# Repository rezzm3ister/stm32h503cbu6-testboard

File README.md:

# stm32h503cbu6-testboard
h503cbu6 testboard based on the previous g4 testboard

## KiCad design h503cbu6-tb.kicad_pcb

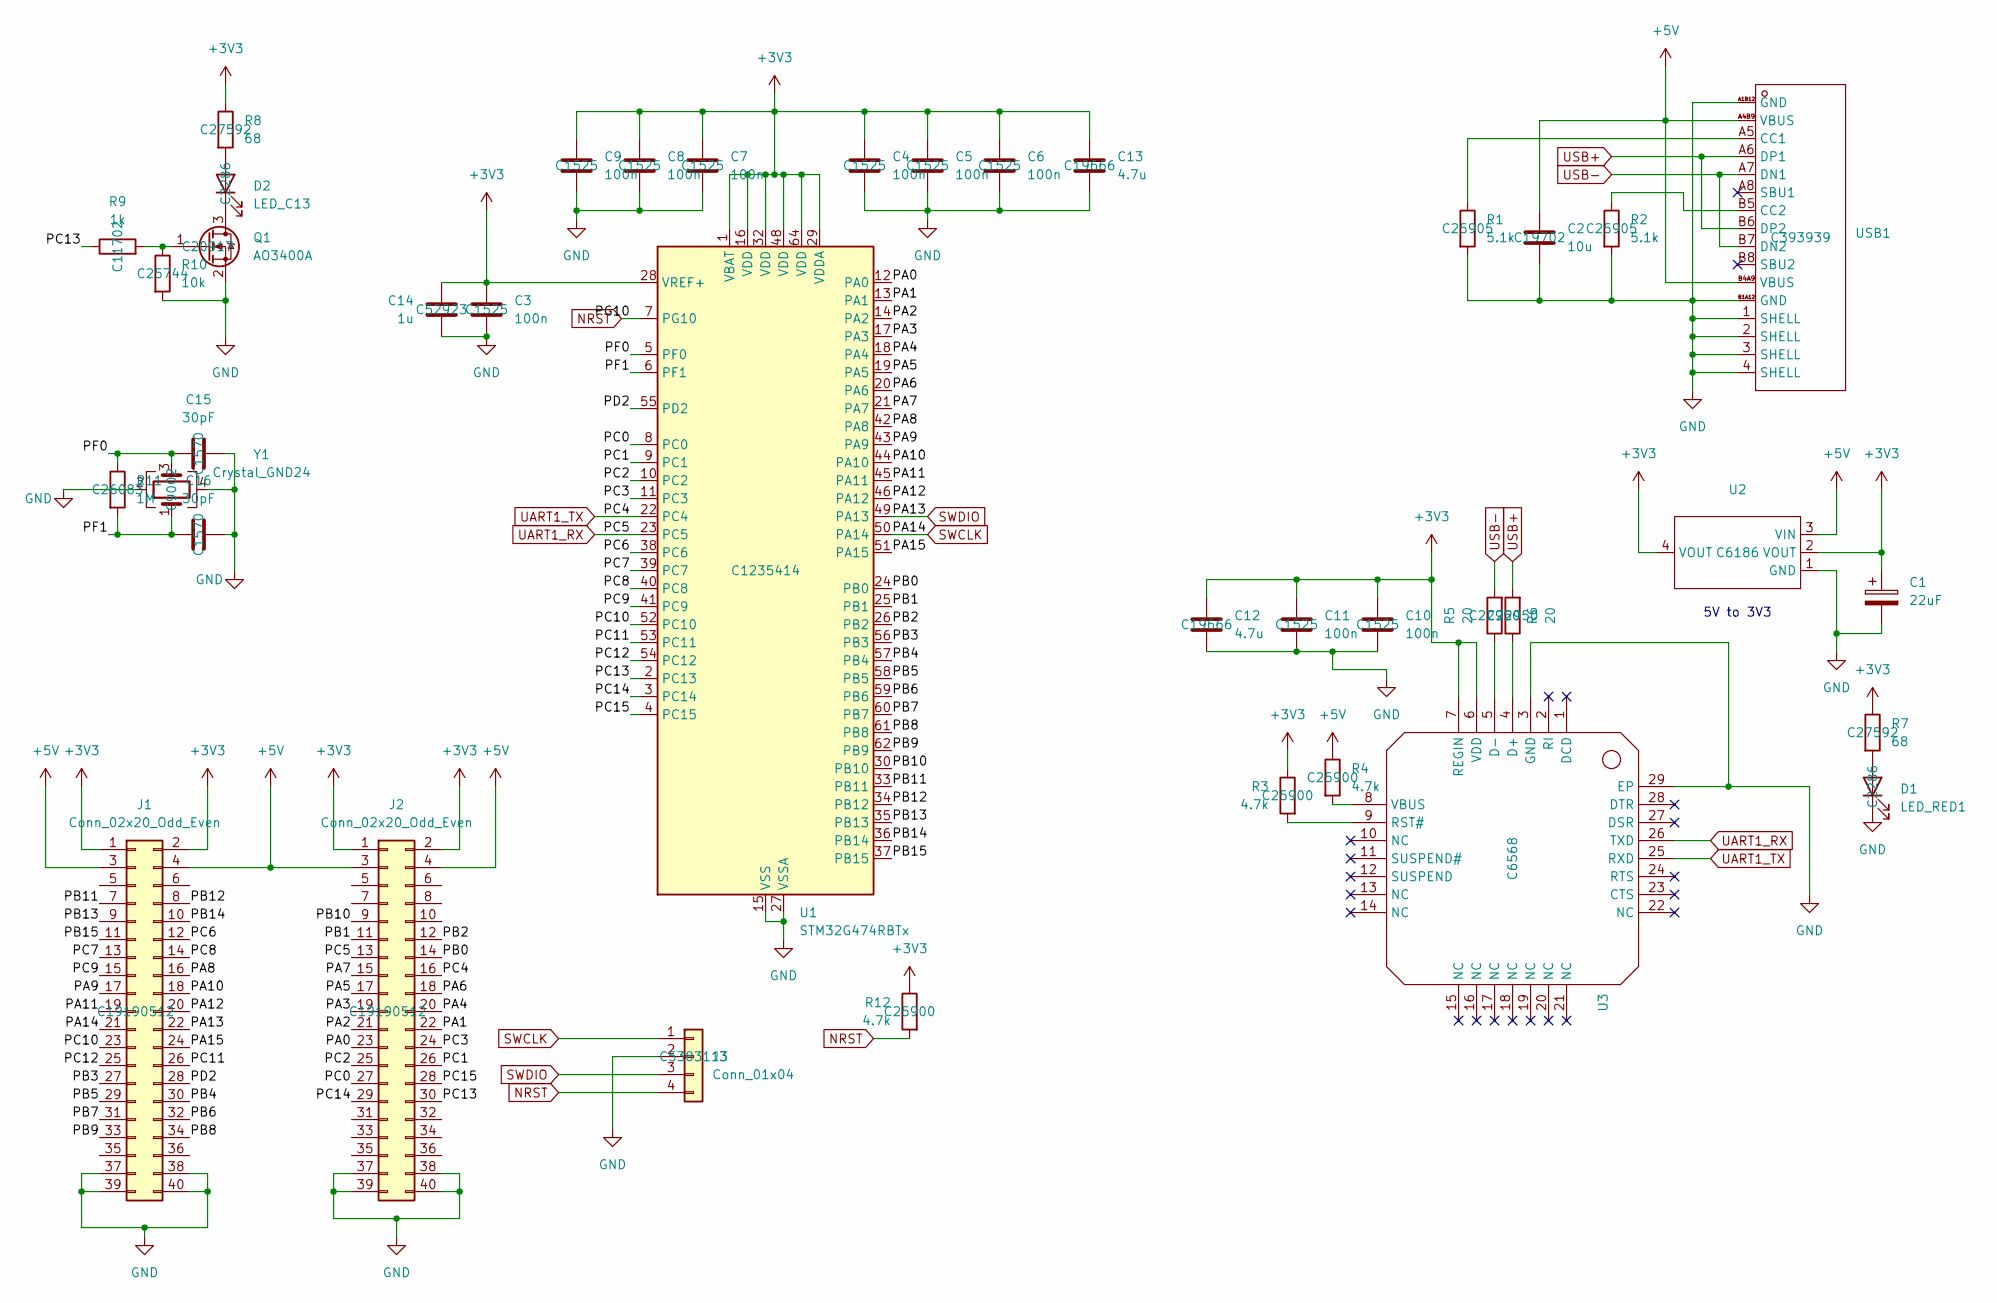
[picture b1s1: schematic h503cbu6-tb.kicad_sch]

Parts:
C1: 22uF; CP_EIA-3216-18_Kemet-A; LCSC C7182
C2: 10u; C_0603_1608Metric; LCSC C19702
C3, C4, C5, C6, C7, C8, C9, C10, C11: 100n; C_0402_1005Metric; LCSC C1525
C12, C13: 4.7u; C_0603_1608Metric; LCSC C19666
C14: 1u; C_0603_1608Metric; LCSC C52923
C15, C16: 30pF; C_0402_1005Metric; LCSC C1570
D1: LED_RED1; LED_0603_1608Metric; LCSC C2286
D2: LED_C13; LED_0603_1608Metric; LCSC C2286
J1, J2: Conn_02x20_Odd_Even; PinHeader_2x20_P2.54mm_Vertical; LCSC C19190512
J3: Conn_01x04; PinHeader_1x04_P2.54mm_Vertical; LCSC C5383113
Q1: AO3400A; SOT-23; LCSC C20917
R1, R2: 5.1k; R_0402_1005Metric; LCSC C25905
R3, R4, R12: 4.7k; R_0402_1005Metric; LCSC C25900
R5, R6: 20; R_0603_1608Metric; LCSC C22950
R7, R8: 68; R_0603_1608Metric; LCSC C27592
R9: 1k; R_0402_1005Metric; LCSC C11702
R10: 10k; R_0402_1005Metric; LCSC C25744
R11: 1M; R_0402_1005Metric; LCSC C26083
U1: STM32G474RBTx; LQFP-64_10x10mm_P0.5mm; LCSC C1235414
U2: AMS1117; Manufacturer Part AMS1117-3.3; LCSC Part Name 输出3.3V 1A
U3: CP2102-WQFN-28_L5.0-W5.0-P0.50-BL-EP3.2; Manufacturer Part CP2102-GMR; LCSC Part Name 单芯片USB转UART桥接器
USB1: USB-C-SMD_TYPE-C16PIN; Manufacturer Part TYPE-C16PIN; LCSC Part Name Type-C 母 卧贴
Y1: Crystal_GND24; Crystal_SMD_3225-4Pin_3.2x2.5mm; LCSC C9002

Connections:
+3V3: C1.1, C3.1, C4.1, C5.1, C6.1, C7.1, C8.1, C9.1, C10.1, C11.1, C12.1, C13.1, C14.1, J1.1, J1.2, J2.1, J2.2, R3.1, R7.1, R8.1, R12.1, U1.1 (VBAT), U1.16 (VDD), U1.28 (VREF+), U1.29 (VDDA), U1.32 (VDD), U1.48 (VDD), U1.64 (VDD), U2.2 (VOUT), U2.4 (VOUT), U3.6 (VDD), U3.7 (REGIN)
+5V: C2.1, J1.3, J1.4, J2.3, J2.4, R4.1, U2.3 (VIN), USB1.A4B9 (VBUS), USB1.B4A9 (VBUS)
/PA0: J2.23, U1.12 (PA0)
/PA1: J2.22, U1.13 (PA1)
/PA2: J2.21, U1.14 (PA2)
/PA3: J2.19, U1.17 (PA3)
/PA4: J2.20, U1.18 (PA4)
/PA5: J2.17, U1.19 (PA5)
/PA6: J2.18, U1.20 (PA6)
/PA7: J2.15, U1.21 (PA7)
/PA8: J1.16, U1.42 (PA8)
/PA9: J1.17, U1.43 (PA9)
/PA10: J1.18, U1.44 (PA10)
/PA11: J1.19, U1.45 (PA11)
/PA12: J1.20, U1.46 (PA12)
/PA15: J1.24, U1.51 (PA15)
/PB0: J2.14, U1.24 (PB0)
/PB1: J2.11, U1.25 (PB1)
/PB2: J2.12, U1.26 (PB2)
/PB3: J1.27, U1.56 (PB3)
/PB4: J1.30, U1.57 (PB4)
/PB5: J1.29, U1.58 (PB5)
/PB6: J1.32, U1.59 (PB6)
/PB7: J1.31, U1.60 (PB7)
/PB8: J1.34, U1.61 (PB8)
/PB9: J1.33, U1.62 (PB9)
/PB10: J2.9, U1.30 (PB10)
/PB11: J1.7, U1.33 (PB11)
/PB12: J1.8, U1.34 (PB12)
/PB13: J1.9, U1.35 (PB13)
/PB14: J1.10, U1.36 (PB14)
/PB15: J1.11, U1.37 (PB15)
/PC0: J2.27, U1.8 (PC0)
/PC1: J2.26, U1.9 (PC1)
/PC2: J2.25, U1.10 (PC2)
/PC3: J2.24, U1.11 (PC3)
/PC6: J1.12, U1.38 (PC6)
/PC7: J1.13, U1.39 (PC7)
/PC8: J1.14, U1.40 (PC8)
/PC9: J1.15, U1.41 (PC9)
/PC10: J1.23, U1.52 (PC10)
/PC11: J1.26, U1.53 (PC11)
/PC12: J1.25, U1.54 (PC12)
/PC13: J2.30, R9.1, U1.2 (PC13)
/PC14: J2.29, U1.3 (PC14)
/PC15: J2.28, U1.4 (PC15)
/PD2: J1.28, U1.55 (PD2)
/PF0: C15.1, R11.1, U1.5 (PF0), Y1.3
/PF1: C16.2, R11.2, U1.6 (PF1), Y1.1
GND: C1.2, C2.2, C3.2, C4.2, C5.2, C6.2, C7.2, C8.2, C9.2, C10.2, C11.2, C12.2, C13.2, C14.2, C15.2, C16.1, D1.1 (K), J1.37, J1.38, J1.39, J1.40, J2.37, J2.38, J2.39, J2.40, J3.2, Q1.2 (S), R1.2, R2.2, R10.2, U1.15 (VSS), U1.27 (VSSA), U1.31 (VSS), U1.47 (VSS), U1.63 (VSS), U2.1 (GND), U3.3 (GND), U3.29 (EP), USB1.1 (SHELL), USB1.2 (SHELL), USB1.3 (SHELL), USB1.4 (SHELL), USB1.A1B12 (GND), USB1.B1A12 (GND), Y1.2, Y1.4
NRST: J3.4, R12.2, U1.7 (PG10)
unnamed: D1.2 (A), R7.2
unnamed: D2.2 (A), R8.2
unnamed: D2.1 (K), Q1.3 (D)
unnamed: Q1.1 (G), R9.2, R10.1
unnamed: R6.1, U3.4 (D+)
unnamed: R5.1, U3.5 (D-)
unnamed: R3.2, U3.9 (RST#)
unnamed: R4.2, U3.8 (VBUS)
unnamed: R1.1, USB1.A5 (CC1)
unnamed: R2.1, USB1.B5 (CC2)
SWCLK: J1.21, J3.1, U1.50 (PA14)
SWDIO: J1.22, J3.3, U1.49 (PA13)
UART1_RX: J2.13, U1.23 (PC5), U3.26 (TXD)
UART1_TX: J2.16, U1.22 (PC4), U3.25 (RXD)
USB+: R6.2, USB1.A6 (DP1), USB1.B6 (DP2)
USB-: R5.2, USB1.A7 (DN1), USB1.B7 (DN2)

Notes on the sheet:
5V to 3V3

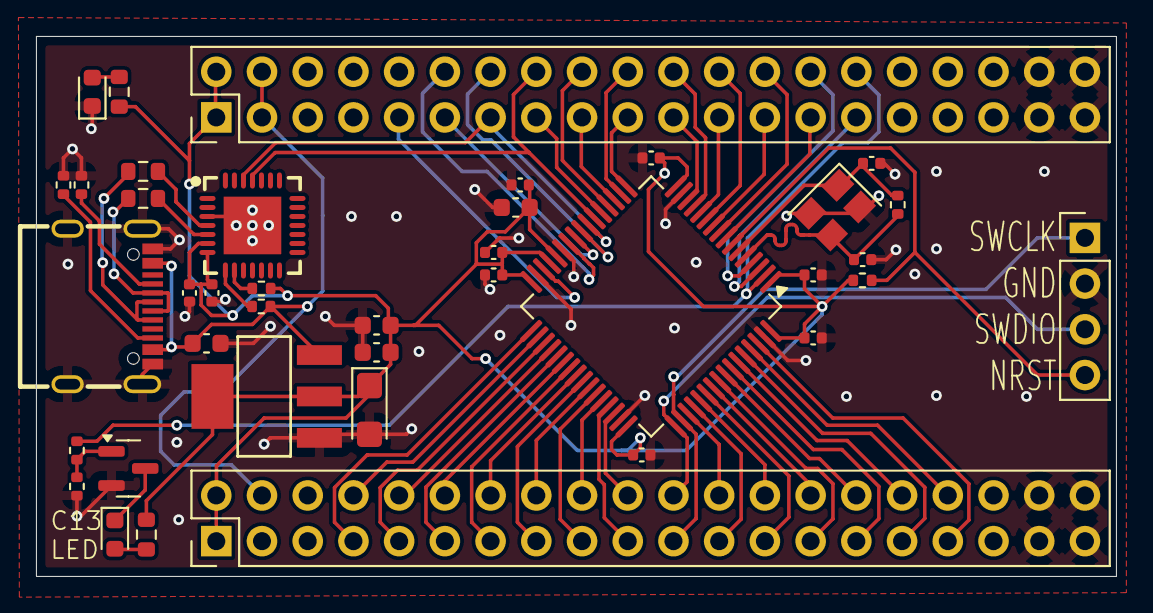
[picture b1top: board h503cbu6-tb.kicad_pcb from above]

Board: 2 copper layers, 60.0 x 30.0 mm, 39 parts (0 on the bottom side), 67 nets.

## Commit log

2026-01-05 added and renamed base files from g4 testboard
